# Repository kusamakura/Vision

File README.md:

# Vision Alt PCB

A PCB for the [Vision keyboard by SatT Keyboards](https://github.com/satt99/Vision) with alternative layout options.

## Notable changes

- R2 2U Backspace
- Left bottom row: from 2U-1U to 1U-2U, add 3U
- Right bottom row: remove 1U-1.75U, add 2.75U
- Nudge P position 0.125 mm to the left

## Layout

## How to use

Use the gerbers, BOM, and CPL files in the [JLCPCB production files folder](./JLCPCB/production_files/). **Set the PCB thickness to 1.2 mm when ordering**; otherwise your PCB will not work with the case.

Prototypes pending to check if this works.

The source files were originally in KiCAD 5, converted to KiCAD 6, then modified.
JLC production output was generated with the [JLC Fabrication Toolkit plugin](https://github.com/bennymeg/JLC-Plugin-for-KiCad).

## Disclaimer

Maintainers and contributors are not liable if you end up with a non-functional PCB. Order at your own risk. Support will not be provided but pull requests will be reviewed and possibly accepted.

## Todo

- [x] Finalize layout changes
- [x] Order prototypes
- [ ] Confirm prototypes
- [ ] Order plates
- [ ] Write firmware

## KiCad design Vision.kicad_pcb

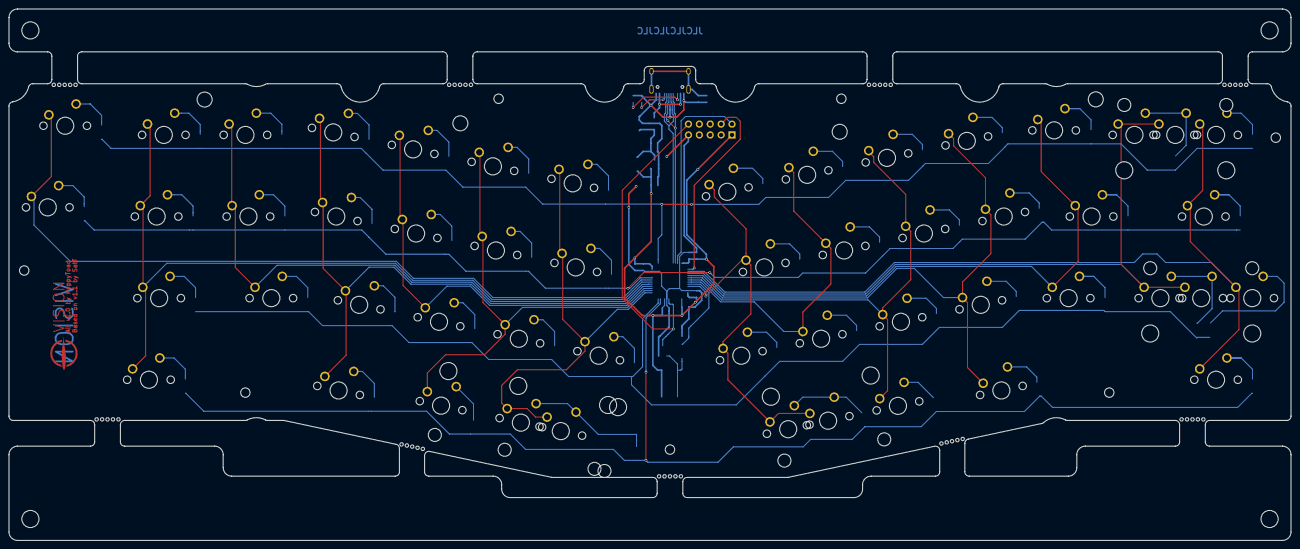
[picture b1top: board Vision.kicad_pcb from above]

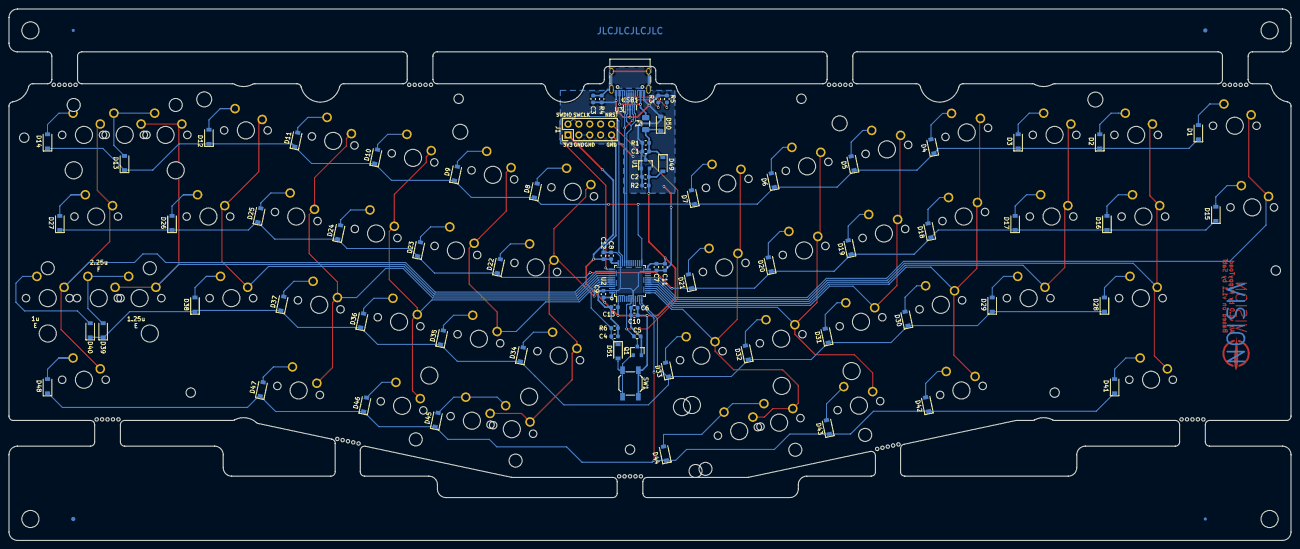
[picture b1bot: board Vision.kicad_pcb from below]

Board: 2 copper layers, 299.2 x 124.0 mm, 145 parts (83 on the bottom side), 77 nets.

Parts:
C1, C2, C10: 1uF; C_0603_1608Metric
C3: 4.7nF; C_0603_1608Metric
C4: 10uF; C_0603_1608Metric
C5, C11, C12: 4.7uF; C_0603_1608Metric
C6: 10nF; C_0603_1608Metric
C7, C8, C9, C13: 100nF; C_0603_1608Metric
D1, D2, D3, D4, D5, D6, D7, D8, D9, D10, D11, D12, D13, D14, D15, D16, D17, D18, D19, D20, D21, D22, D23, D24, D25, D26, D27, D28, D29, D30, D31, D32, D33, D34, D35, D36, D37, D38, D39, D40, D41, D42, D43, D44, D45, D46, D47, D48, D51: 1N4148W; D_SOD-123
D49: BAT41ZFILM; D_SOD-123
D50: SMF9.0CA; D_SOD-123
F1: 500mA; Fuse_1206_3216Metric
H1: LOGO1; logo1
H2: LOGO2; logo2
H3, H4: FIDUCIAL; Fiducial_0.75mm_Mask2.25mm
H5, H6: FIDUCIAL; Fiducial_1mm_Mask3mm
H7, H8, H9, H10, H11, H12, H13, H14, H15: MOUSEBITES; breakaway-mousebites
J1: Conn_ARM_JTAG_SWD_10; PinHeader_2x05_P2.54mm_Vertical
K_,1: MX-1U; MXOnly-1U-NoLED
K_.1: MX-1U; MXOnly-1U-NoLED
K_;1: MX-1U; MXOnly-1U-NoLED
K_A1: MX-1U; MXOnly-1U-NoLED
K_ALT1, K_ALT2: MX-1.5U; MXOnly-1.5U-NoLED
K_B1, K_B2: MX-1U; MXOnly-1U-NoLED
K_BSPC1: MX-1U; MXOnly-1U-NoLED
K_BSPC2: MX-2U; MXOnly-2U-NoLED
K_C1: MX-1U; MXOnly-1U-NoLED
K_CTRL1, K_CTRL2: MX-1.5U; MXOnly-1.5U-NoLED
K_D1: MX-1U; MXOnly-1U-NoLED
K_DEL1: MX-1U; MXOnly-1U-NoLED
K_E1: MX-1U; MXOnly-1U-NoLED
K_ENTER1: MX-1.75U; MXOnly-1.75U-NoLED
K_ESC1: MX-1U; MXOnly-1U-NoLED
K_F1: MX-1U; MXOnly-1U-NoLED
K_FN1: MX-1U; MXOnly-1U-NoLED
K_G1: MX-1U; MXOnly-1U-NoLED
K_H1: MX-1U; MXOnly-1U-NoLED
K_I1: MX-1U; MXOnly-1U-NoLED
K_J1: MX-1U; MXOnly-1U-NoLED
K_K1: MX-1U; MXOnly-1U-NoLED
K_L1: MX-1U; MXOnly-1U-NoLED
K_M1: MX-1U; MXOnly-1U-NoLED
K_N1: MX-1U; MXOnly-1U-NoLED
K_O1: MX-1U; MXOnly-1U-NoLED
K_P1: MX-1U; MXOnly-1U-NoLED
K_PGDN1: MX-1U; MXOnly-1U-NoLED
K_PGUP1: MX-1U; MXOnly-1U-NoLED
K_Q1: MX-1U; MXOnly-1U-NoLED
K_R1: MX-1U; MXOnly-1U-NoLED
K_S1: MX-1U; MXOnly-1U-NoLED
K_SHIFT1: MX-1.75U; MXOnly-1.75U-NoLED
K_SHIFT2: MX-1.25U; MXOnly-1.25U-NoLED
K_SHIFT3: MX-2.25U; MXOnly-2.25U-NoLED
K_SPC1: MX-2U; MXOnly-2U-ReversedStabilizers-NoLED
K_SPC2: MX-1.75U; MXOnly-1.75U-NoLED
K_SPC3: MX-3U; MXOnly-3U-ReversedStabilizers-NoLED
K_SPC4: MX-2.75U; MXOnly-2.75U-ReversedStabilizers-NoLED
K_T1: MX-1U; MXOnly-1U-NoLED
K_TAB1: MX-1.25U; MXOnly-1.25U-NoLED
K_U1: MX-1U; MXOnly-1U-NoLED
K_V1: MX-1U; MXOnly-1U-NoLED
K_W1: MX-1U; MXOnly-1U-NoLED
K_WIN1, K_WIN2: MX-1U; MXOnly-1U-NoLED
K_X1: MX-1U; MXOnly-1U-NoLED
K_Y1: MX-1U; MXOnly-1U-NoLED
K_Z1: MX-1U; MXOnly-1U-NoLED
Q1: DTC123J; SOT-23
R1, R2, R6: 100k; R_0603_1608Metric
R3, R5: 5.1k; R_0603_1608Metric
R4: 1M; R_0603_1608Metric
SW1: SW_Push; SW_SPST_SKQG_WithoutStem
U1: MCP1700-3002E_SOT23; SOT-23
U2: STM32F072CBUx; LQFP-48_7x7mm_P0.5mm
U3: TPD4E05U06DQAR; USON-TPDxE05U06
USB1: HRO-TYPE-C-31-M-12; USB_C_Receptacle_HRO_TYPE-C-31-M-12

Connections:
+3V3: C2.1, C6.1, C7.1, C8.1, C9.1, C10.1, C11.1, C12.1, C13.1, D49.2 (A), J1.1 (VTref), R2.2, SW1.1, U1.2 (VO), U2.1 (VBAT), U2.9 (VDDA), U2.24 (VDD), U2.36 (VDDIO2), U2.48 (VDD)
+5V: C1.1, D49.1 (K), D50.1 (A1), F1.1, R1.2, U1.3 (VI)
BOOT0: C4.1, D51.1 (K), R6.2, U2.44 (BOOT0)
COL0: K_PGDN1.1 (COL), K_PGUP1.1 (COL), U2.19 (PB1)
COL1: K_CTRL1.1 (COL), K_ESC1.1 (COL), K_SHIFT1.1 (COL), K_TAB1.1 (COL), U2.18 (PB0)
COL2: K_A1.1 (COL), K_Q1.1 (COL), K_Z1.1 (COL), U2.17 (PA7)
COL3: K_ALT1.1 (COL), K_S1.1 (COL), K_W1.1 (COL), K_X1.1 (COL), U2.16 (PA6)
COL4: K_C1.1 (COL), K_D1.1 (COL), K_E1.1 (COL), U2.15 (PA5)
COL5: K_F1.1 (COL), K_R1.1 (COL), K_V1.1 (COL), K_WIN1.1 (COL), U2.14 (PA4)
COL6: K_B1.1 (COL), K_G1.1 (COL), K_SPC1.1 (COL), K_SPC3.1 (COL), K_T1.1 (COL), U2.13 (PA3)
COL7: K_B2.1 (COL), K_H1.1 (COL), K_SPC2.1 (COL), K_SPC4.1 (COL), K_Y1.1 (COL), U2.45 (PB8)
COL8: K_J1.1 (COL), K_N1.1 (COL), K_U1.1 (COL), U2.43 (PB7)
COL9: K_I1.1 (COL), K_K1.1 (COL), K_M1.1 (COL), K_WIN2.1 (COL), U2.42 (PB6)
COL10: K_,1.1 (COL), K_ALT2.1 (COL), K_L1.1 (COL), K_O1.1 (COL), U2.41 (PB5)
COL11: K_.1.1 (COL), K_;1.1 (COL), K_P1.1 (COL), U2.40 (PB4)
COL12: K_BSPC1.1 (COL), K_BSPC2.1 (COL), K_SHIFT2.1 (COL), K_SHIFT3.1 (COL), U2.39 (PB3)
COL13: K_CTRL2.1 (COL), K_DEL1.1 (COL), K_ENTER1.1 (COL), K_FN1.1 (COL), U2.38 (PA15)
D+: U2.33 (PA12), U3.1 (D1+), U3.4 (D2+), U3.7 (NC), U3.10 (NC)
D-: U2.32 (PA11), U3.2 (D1-), U3.5 (D2-), U3.6 (NC), U3.9 (NC)
GND: C1.2, C2.2, C3.1, C4.2, C5.2, C6.2, C7.2, C8.2, C9.2, C10.2, C11.2, C12.2, C13.2, D50.2 (A2), J1.3 (GND), J1.5 (GND), J1.9 (GNDDetect), Q1.2 (E), R1.1, R2.1, R3.1, R4.1, R5.1, R6.1, U1.1 (GND), U2.8 (VSSA), U2.23 (VSS), U2.35 (VSS), U2.47 (VSS), U3.3 (GND), U3.8 (GND)
NRST: C5.1, J1.10 (~RESET), Q1.3 (C), U2.7 (NRST)
unnamed: C3.2, R4.2, USB1.S1
unnamed: D1.2 (A), K_PGUP1.2 (ROW)
unnamed: D2.2 (A), K_ESC1.2 (ROW)
unnamed: D3.2 (A), K_Q1.2 (ROW)
unnamed: D4.2 (A), K_W1.2 (ROW)
unnamed: D5.2 (A), K_E1.2 (ROW)
unnamed: D6.2 (A), K_R1.2 (ROW)
unnamed: D7.2 (A), K_T1.2 (ROW)
unnamed: D8.2 (A), K_Y1.2 (ROW)
unnamed: D9.2 (A), K_U1.2 (ROW)
unnamed: D10.2 (A), K_I1.2 (ROW)
unnamed: D11.2 (A), K_O1.2 (ROW)
unnamed: D12.2 (A), K_P1.2 (ROW)
unnamed: D13.2 (A), K_BSPC1.2 (ROW), K_BSPC2.2 (ROW)
unnamed: D14.2 (A), K_DEL1.2 (ROW)
unnamed: D15.2 (A), K_PGDN1.2 (ROW)
unnamed: D16.2 (A), K_TAB1.2 (ROW)
unnamed: D17.2 (A), K_A1.2 (ROW)
unnamed: D18.2 (A), K_S1.2 (ROW)
unnamed: D19.2 (A), K_D1.2 (ROW)
unnamed: D20.2 (A), K_F1.2 (ROW)
unnamed: D21.2 (A), K_G1.2 (ROW)
unnamed: D22.2 (A), K_H1.2 (ROW)
unnamed: D23.2 (A), K_J1.2 (ROW)
unnamed: D24.2 (A), K_K1.2 (ROW)
unnamed: D25.2 (A), K_L1.2 (ROW)
unnamed: D26.2 (A), K_;1.2 (ROW)
unnamed: D27.2 (A), K_ENTER1.2 (ROW)
unnamed: D28.2 (A), K_SHIFT1.2 (ROW)
unnamed: D29.2 (A), K_Z1.2 (ROW)
unnamed: D30.2 (A), K_X1.2 (ROW)
unnamed: D31.2 (A), K_C1.2 (ROW)
unnamed: D32.2 (A), K_V1.2 (ROW)
unnamed: D33.2 (A), K_B1.2 (ROW)
unnamed: D34.2 (A), K_B2.2 (ROW)
unnamed: D35.2 (A), K_N1.2 (ROW)
unnamed: D36.2 (A), K_M1.2 (ROW)
unnamed: D37.2 (A), K_,1.2 (ROW)
unnamed: D38.2 (A), K_.1.2 (ROW)
unnamed: D39.2 (A), K_SHIFT2.2 (ROW), K_SHIFT3.2 (ROW)
unnamed: D40.2 (A), K_FN1.2 (ROW)
unnamed: D41.2 (A), K_CTRL1.2 (ROW)
unnamed: D42.2 (A), K_ALT1.2 (ROW)
unnamed: D43.2 (A), K_WIN1.2 (ROW)
unnamed: D44.2 (A), K_SPC1.2 (ROW), K_SPC3.2 (ROW)
unnamed: D45.2 (A), K_SPC2.2 (ROW), K_SPC4.2 (ROW)
unnamed: D46.2 (A), K_WIN2.2 (ROW)
unnamed: D47.2 (A), K_ALT2.2 (ROW)
unnamed: D48.2 (A), K_CTRL2.2 (ROW)
unnamed: D51.2 (A), Q1.1 (B), SW1.2
ROW0: D1.1 (K), D2.1 (K), D3.1 (K), D4.1 (K), D5.1 (K), D6.1 (K), D7.1 (K), D8.1 (K), D9.1 (K), D10.1 (K), D11.1 (K), D12.1 (K), D13.1 (K), D14.1 (K), U2.25 (PB12)
ROW1: D15.1 (K), D16.1 (K), D17.1 (K), D18.1 (K), D19.1 (K), D20.1 (K), D21.1 (K), D22.1 (K), D23.1 (K), D24.1 (K), D25.1 (K), D26.1 (K), D27.1 (K), U2.20 (PB2)
ROW2: D28.1 (K), D29.1 (K), D30.1 (K), D31.1 (K), D32.1 (K), D33.1 (K), D34.1 (K), D35.1 (K), D36.1 (K), D37.1 (K), D38.1 (K), D39.1 (K), D40.1 (K), U2.12 (PA2)
ROW3: D41.1 (K), D42.1 (K), D43.1 (K), D44.1 (K), D45.1 (K), D46.1 (K), D47.1 (K), D48.1 (K), U2.11 (PA1)
SWCLK: J1.4 (SWDCLK/TCK), U2.37 (PA14)
SWDIO: J1.2 (SWDIO/TMS), U2.34 (PA13)

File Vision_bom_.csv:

Component,Description,Part,References,Value,Footprint,Quantity Per PCB,Datasheet
1,"Unpolarized capacitor, small symbol",C_Small,C7 C8 C9 C13,100nF,C_0603_1608Metric,4,
2,"Unpolarized capacitor, small symbol",C_Small,C6,10nF,C_0603_1608Metric,1,
3,"Unpolarized capacitor, small symbol",C_Small,C4,10uF,C_0603_1608Metric,1,~
4,"Unpolarized capacitor, small symbol",C_Small,C1 C2 C10,1uF,C_0603_1608Metric,3,~
5,"Unpolarized capacitor, small symbol",C_Small,C3,4.7nF,C_0603_1608Metric,1,~
6,"Unpolarized capacitor, small symbol",C_Small,C5 C11 C12,4.7uF,C_0603_1608Metric,3,~
7,"Diode, small symbol",D_Small,D1 D2 D3 D4 D5 D6 D7 D8 D9 D10 D11 D12 D13 D14 D15 D16 D17 D18 D19 D20 D21 D22 D23 D24 D25 D26 D27 D28 D29 D30 D31 D32 D33 D34 D35 D36 D37 D38 D39 D40 D41 D42 D43 D44 D45 D46 D47 D48 D51,1N4148W,D_SOD-123,49,
8,"Schottky diode, small symbol",D_Schottky_Small,D49,BAT41ZFILM,D_SOD-123,1,~
9,Bidirectional transient-voltage-suppression diode,D_TVS,D50,SMF9.0CA,D_SOD-123,1,~
10,"Resettable fuse, polymeric positive temperature coefficient, small symbol",Polyfuse_Small,F1,500mA,Fuse_1206_3216Metric,1,
11,"Cortex Debug Connector, standard ARM Cortex-M SWD and JTAG interface",Conn_ARM_JTAG_SWD_10,J1,Conn_ARM_JTAG_SWD_10,PinHeader_2x05_P2.54mm_Vertical,1,http://infocenter.arm.com/help/topic/com.arm.doc.ddi0314h/DD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
12,"Digital NPN Transistor, 2k2/47k, SOT-23",DTC123J,Q1,DTC123J,SOT-23,1,
13,"Resistor, small symbol",R_Small,R1 R2 R6,100k,R_0603_1608Metric,3,~
14,"Resistor, small symbol",R_Small,R4,1M,R_0603_1608Metric,1,~
15,"Resistor, small symbol",R_Small,R3 R5,5.1k,R_0603_1608Metric,2,
16,"Push button switch, generic, two pins",SW_Push,SW1,SW_Push,SW_SPST_SKQG_WithoutStem,1,
17,"250mA Low Quiscent Current LDO, 3.0V output, SOT-23",MCP1700-3002E_SOT23,U1,MCP1700-3002E_SOT23,SOT-23,1,http://ww1.microchip.com/downloads/en/DeviceDoc/20001826C.pdf
18,"ARM Cortex-M0 MCU, 128KB flash, 16KB RAM, 48MHz, 2-3.6V, 37 GPIO, LQFP-48",STM32F072CBTx,U2,STM32F072CBUx,LQFP-48_7x7mm_P0.5mm,1,http://www.st.com/st-web-ui/static/active/en/resource/techni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
19,,TPD4E05U06DQAR,U3,TPD4E05U06DQAR,USON-TPDxE05U06,1,
20,,HRO-TYPE-C-31-M-12,USB1,HRO-TYPE-C-31-M-12,HRO-TYPE-C-31-M-12-Assembly,1,





Component Groups:,20
Component Count:,78
Fitted Components:,78
Number of PCBs:,1
Total components:,78
Schematic Version:,
Schematic Date:,
PCB Variant:,default
BoM Date:,2020/06/13 17:00:34
Schematic Source:,Vision.sch
KiCad Version:,Eeschema (5.1.4)-1

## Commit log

2020-05-02 Add gitignore reset cache
2020-05-02 Rename project
2020-05-03 Updated submodule MX_Alps_Hybrid.pretty
2020-05-03 Updated submodule random-keyboard-parts.pretty
2020-05-03 Update schematics
2020-05-03 Set switch position
2020-05-04 Fix switch position
2020-05-05 Route PCB
2020-05-05 Add edgerails
2020-05-05 Fix gerber
2020-05-06 Fix fiducials
2020-05-06 Add BOM
2020-06-13 Update pcb shape
2020-06-13 Add files for Elecrow PCBA
2020-06-20 Update Elecrow PCBA files
2020-06-20 Update revision number
2020-06-21 Fix routing
2020-06-21 Update PCB
2020-06-21 Add silk for different layouts
2020-06-21 Fix overlapping silk
2023-02-14 Create alt rev 1 with JLC production files
2023-07-08 Update BOM and CPL
2023-07-08 Add plates and update readme
2023-07-08 Nudge P switch position to the left, add custom plates
2023-07-08 Update default gerber output dir
2023-07-08 Fix footprints
2023-07-08 Use native Kicad USB-C footprint
2023-07-09 Final pre-proto changes
